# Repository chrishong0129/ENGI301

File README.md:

# ENGI301
Intro to Practical EE

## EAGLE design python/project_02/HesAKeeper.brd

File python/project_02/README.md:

ENGI 301 Project_02

Project Name: He's a Keeper
Project Owner: Christopher Hong
Date: May 2, 2022

He's a Keeper is a goalkeeper reflex training game modified from the classic Whac-a-mole game. 
The circuit design of He's a Keeper was initially on a breadboard, but now will be replaced with a new PCB design.
The PCB is designed to be circular, matching the shape of circular buttons!
Unfortunately, the PCB design was not completed in time.
The schematics are almost complete, but the layout still needs a decent bit of work to be done.

There are 6 buttons used that extend from the PCB in the center. 
Each button is fit into a 3D-printed enclosure with suction cups.
Feel free to add male-female jumper wires if you want to position the buttons further away.

Each game will start with a 3-sec countdown and go through 20 rounds.
In each round, one of the 6 buttons will light up randomly with the buzzer. 
Hit the lit button as quick as possible! The display will show you how much time you took to hit it.
The time delay between each round is randomized, so be alert!
At the end of the game, the display will show you the average time you took to hit the correct button.
There is a restart button on the PCB if you want to play another round!

Check the Hackster page for instructions and a demo video: 
https://www.hackster.io/456557/he-s-a-keeper-694cbb

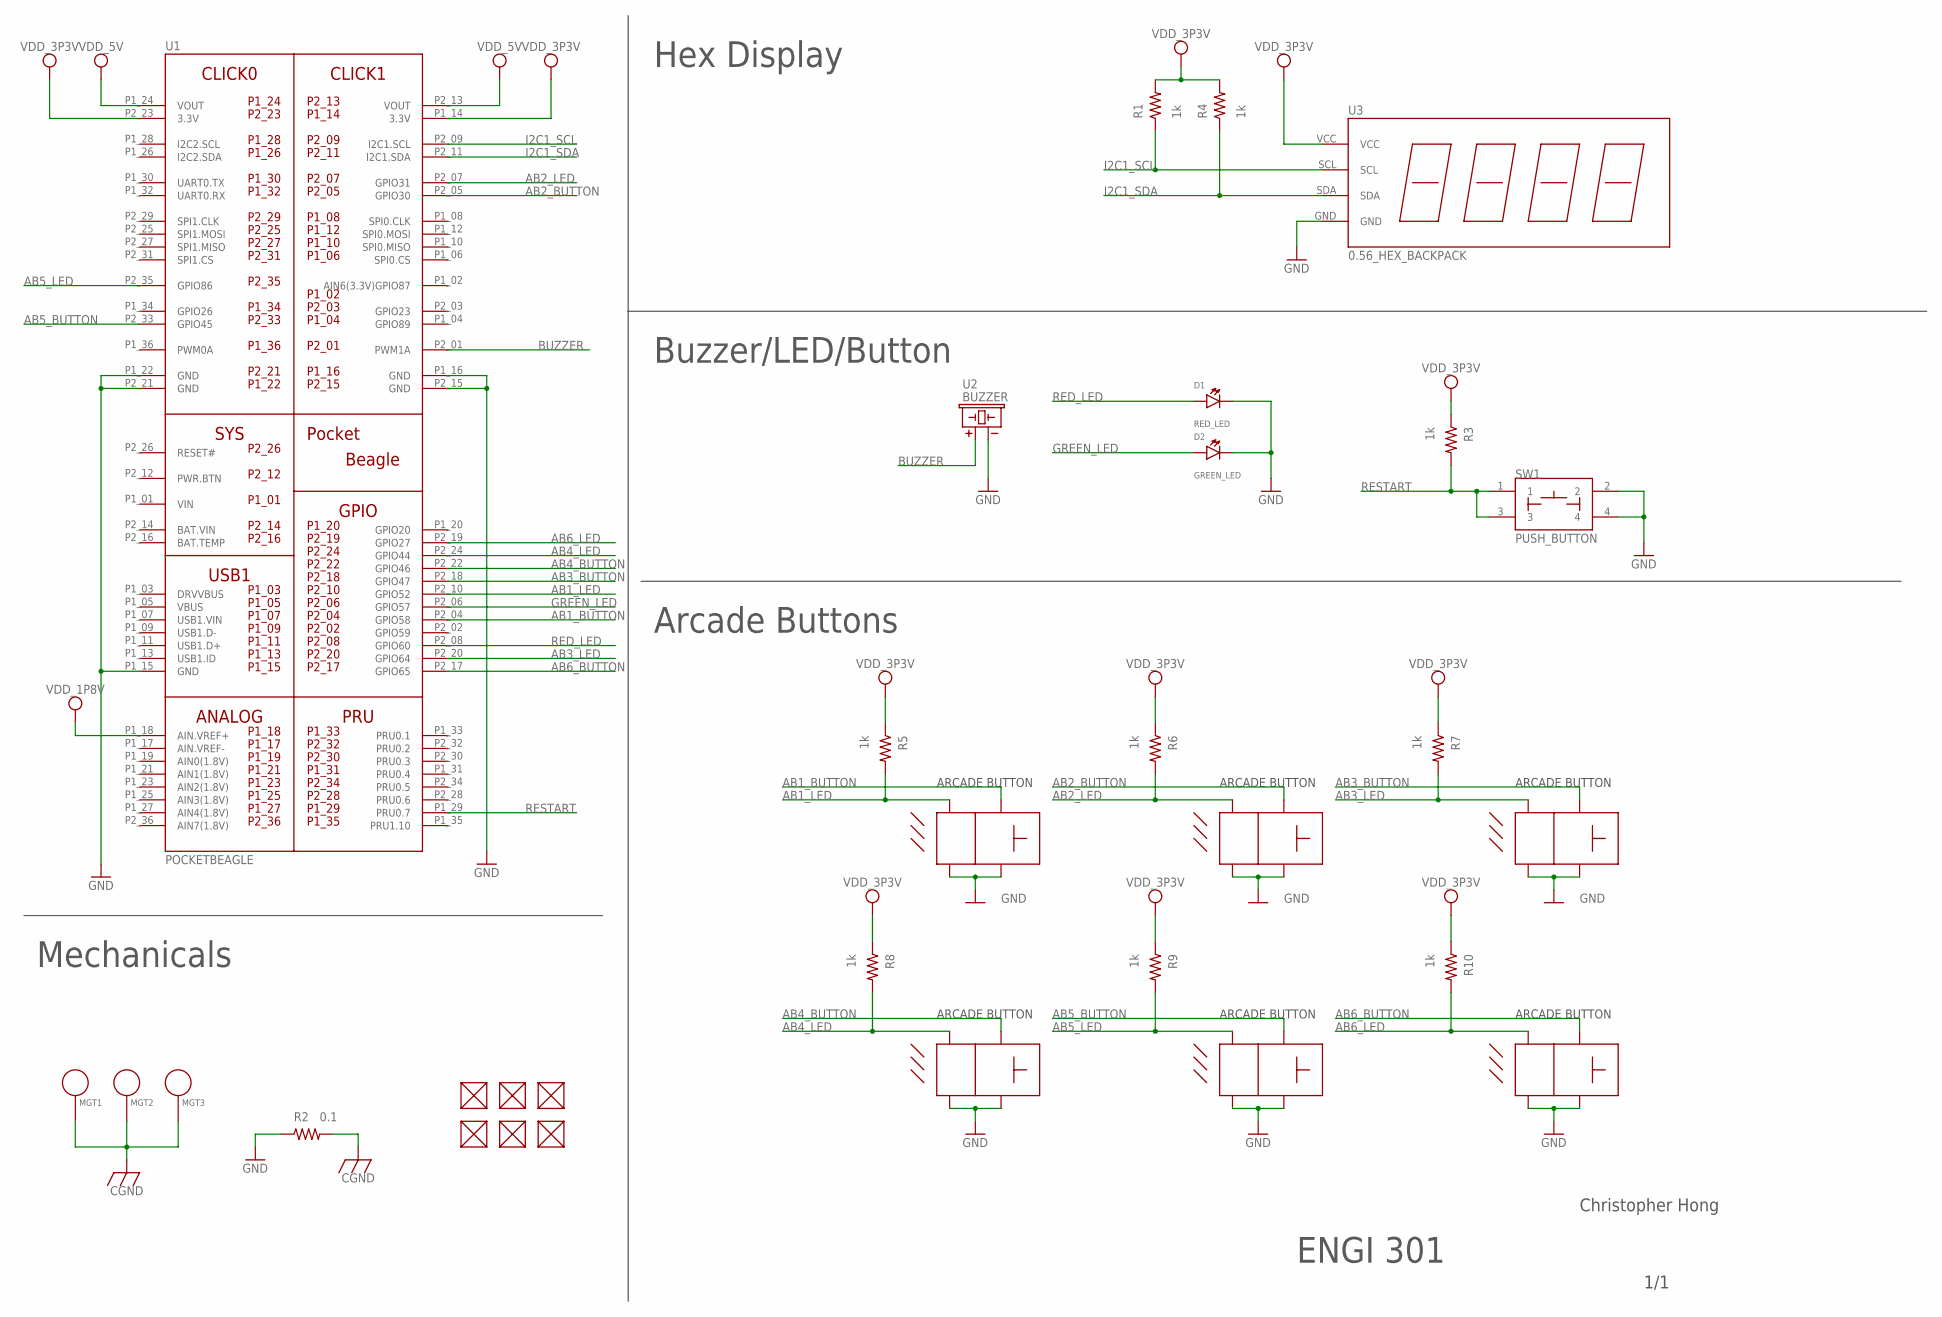
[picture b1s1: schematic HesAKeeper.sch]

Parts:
AB1, AB2, AB3, AB4, AB5, AB6: ARCADE_BUTTON
D1: RED_LED; EIA-STD
D2: GREEN_LED; EIA-STD
FUD1, FUD2, FUD3, FUD4, FUD5, FUD6: FIDUCIAL; FIDUCIAL_40MIL
MGT1, MGT2, MGT3: MOUNTING_HOLE
R1, R3, R4, R5, R6, R7, R8, R9, R10: 1k; R0603
R2: 0.1; R0603
SW1: PUSH_BUTTON; BUTTON_12.5MM
U1: POCKETBEAGLE
U2: BUZZER; BUZZER_6.5MM
U3: 0.56_HEX_BACKPACK

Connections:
AB1_BUTTON: AB1.BUTTON_ANODE, U1.P2_04 (GPIO58)
AB1_LED: AB1.LED_ANODE, R5.2, U1.P2_10 (GPIO52)
AB2_BUTTON: AB2.BUTTON_ANODE, U1.P2_05 (GPIO30)
AB2_LED: AB2.LED_ANODE, R6.2, U1.P2_07 (GPIO31)
AB3_BUTTON: AB3.BUTTON_ANODE, U1.P2_18 (GPIO47)
AB3_LED: AB3.LED_ANODE, R7.2, U1.P2_20 (GPIO64)
AB4_BUTTON: AB4.BUTTON_ANODE, U1.P2_22 (GPIO46)
AB4_LED: AB4.LED_ANODE, R8.2, U1.P2_24 (GPIO44)
AB5_BUTTON: AB5.BUTTON_ANODE, U1.P2_33 (GPIO45)
AB5_LED: AB5.LED_ANODE, R9.2, U1.P2_35 (GPIO86)
AB6_BUTTON: AB6.BUTTON_ANODE, U1.P2_17 (GPIO65)
AB6_LED: AB6.LED_ANODE, R10.2, U1.P2_19 (GPIO27)
BAT.VIN: U1.P2_14 (BAT.VIN)
BUZZER: U1.P2_01 (PWM1A), U2.+
CGND: MGT1.P$1, MGT2.P$1, MGT3.P$1, R2.2
GND: AB1.BUTTON_CATHODE, AB1.LED_CATHODE, AB2.BUTTON_CATHODE, AB2.LED_CATHODE, AB3.BUTTON_CATHODE, AB3.LED_CATHODE, AB4.BUTTON_CATHODE, AB4.LED_CATHODE, AB5.BUTTON_CATHODE, AB5.LED_CATHODE, AB6.BUTTON_CATHODE, AB6.LED_CATHODE, D1.CATHODE, D2.CATHODE, R2.1, U1.P1_15 (GND), U1.P1_16 (GND), U1.P1_22 (GND), U1.P2_15 (GND), U1.P2_21 (GND), U2.-, U3.GND
GREEN_LED: D2.ANODE, U1.P2_06 (GPIO57)
I2C1_SCL: R1.1, U1.P2_09 (I2C1.SCL), U3.SCL
I2C1_SDA: R4.1, U1.P2_11 (I2C1.SDA), U3.SDA
unnamed: SW1.2, SW1.4
RED_LED: D1.ANODE, U1.P2_08 (GPIO60)
RESTART: R3.2, SW1.1, SW1.3, U1.P1_29 (PRU0.7)
VDD_1P8V: U1.P1_18 (AIN.VREF+)
VDD_3P3V: R1.2, R3.1, R4.2, R5.1, R6.1, R7.1, R8.1, R9.1, R10.1, U1.P1_14 (3.3V), U1.P2_23 (3.3V), U3.VCC
VDD_5V: U1.P1_24 (VOUT), U1.P2_13 (VOUT)
VIN: U1.P1_01 (VIN)

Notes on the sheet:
1/1
Christopher Hong
Arcade Buttons
Mechanicals
Buzzer/LED/Button
Hex Display
ENGI 301

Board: 2 copper layers, 31 parts (4 on the bottom side), 23 nets, no tracks yet.

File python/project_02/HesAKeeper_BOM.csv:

"Qty";"Value";"Device";"Package";"Parts";"Description";"";
"1";"0.1";"R_R0603";"R0603";"R2";"RESISTOR, American symbol";"";
"1";"0.56_HEX_BACKPACK";"0.56_HEX_BACKPACK";"0.56_HEX_BACKPACK";"U3";"0.56" LED HEX Backback - Adafruit HT16K33 -";"";
"9";"1k";"R_R0603";"R0603";"R1, R3, R4, R5, R6, R7, R8, R9, R10";"RESISTOR, American symbol";"";
"6";"ARCADE_BUTTON";"ARCADE_BUTTON";"ARCADE_BUTTON";"AB1, AB2, AB3, AB4, AB5, AB6";"Arcade Button for He's A Keeper Project";"";
"1";"BUZZER";"BUZZER";"BUZZER_6.5MM";"U2";"CEM-1203 Buzzer";"";
"6";"FIDUCIAL";"FIDUCIAL";"FIDUCIAL_40MIL";"FUD1, FUD2, FUD3, FUD4, FUD5, FUD6";"";"";
"1";"GREEN_LED";"LED";"EIA-STD";"D2";"EIA-STD LED, LTST-C191TBKT";"";
"3";"MOUNTING_HOLE";"MOUNTING_HOLE";"MOUNTING_HOLE";"MGT1, MGT2, MGT3";"Chassis Mounting Hole w/GND connection ability";"";
"1";"POCKETBEAGLE";"POCKETBEAGLE";"POCKETBEAGLE";"U1";"";"";
"1";"PUSH_BUTTON";"PUSH_BUTTON";"BUTTON_12.5MM";"SW1";"";"";
"1";"RED_LED";"LED";"EIA-STD";"D1";"EIA-STD LED, LTST-C191TBKT";"";

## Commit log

2022-02-16 updated file
2022-04-05 adding files
2022-05-02 Create project_02
